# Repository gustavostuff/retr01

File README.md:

Retr01 is an MCU-assisted 8-bit gaming system for arcade and console setups, plus an emulator and a studio for making games and content.

Hardware remains in active development/design. Software, tooling, and documentation track that ongoing specification. The board layout shown above is an early revision and is intended to approximate the planned main PCB.

## Inspirations

1. **NES: readable limits and bold color.** Retr01 uses a 64-color global palette, with up to 25 colors visible on screen at once. Those limits are on purpose. They keep the graphics simple and give every color choice more weight.
2. **SNES: depth without unnecessary complexity.** Two true background planes and pixel-level transparency enable real parallax, layered scenery, and richer scene composition while keeping the graphics pipeline understandable and close to the hardware.
3. **[GameTank](https://gametank.zone/): Open source retro console.** The primary modern inspiration. Retr01 takes the same core ideas of a modest resolution, physical (small) cartridges and a readable multi-chip design that stays explicit instead of hiding behind an FPGA.

## Graphics

The playfield is 128x120 (chunky pixels) scaled to 2x. This means the final render is 256x240, the exact same resolution as the NES, Sega Master System, among others. A whole _game screen_ is 16 tiles wide and 15 tiles tall (a nametable is 240 tile index bytes + 240 _attr_ bytes).

On a higher level, graphics are based on worlds and screens: up to 8 worlds, 64 screens each. That's 512 _TV screens_ of real state + some special/extra screens, PRG, Game music, Game _entities_, etc. All within a 512KB cartridge.

Entities are abstract objects like enemies, players, projectiles, etc. They're made from states, frames, and sprites (a _state_ being something like idle, running, or crouching).

Graphics are tile based, 8x8 pixels, 2bpp.

## Audio

Retr01 uses 8 channels, 5 meant to be used for BGM and the rest for SFX. 

PRG writes notes and a helper chip (an AVR128DB28) mixes them to analog output. The Adventure Kid Waveforms library is used as a built-in sound repository. See [sound.md](docs/sound.md).

## Hardware

The design uses a compact, mostly THT main system board with 19 ICs (CPU + MCUs + SPLDs + some 74xx glue) for both home-console and arcade cabinet builds. That is:

* Home console: TRS ports for the pads. Picture and sound leave on one Kycon KMDGX-9S-AS 9-pin mini-DIN. RGB, CSYNC, composite, mono audio, and +5 V. This is the exact same AV port that the Sega Genesis 2 and Mega Drive 2 made famous.

* Arcade: the same mini-DIN for picture and sound, plus 2x5 headers for sticks and buttons. The JAMMA edge shares those header nets for the controls, and it shares +5 V and GND.

As for the cartridge, it's a small PCB (close to Game Boy size) with an SST39SF040-55-4C-NHE in a PLCC-32 socket, plus a small 8-pin EEPROM for saves. The socket keeps the cart PCB through-hole. 18 gold fingers per side.

Game pads are planned to use a 3-wire connection through any regular male to male audio aux cable (TRS ports on both the main PCB and the pads PCB). A serial protocol + ATtiny chips (on the pads board) will take care of communications.

Retr01 is not a pure TTL/discrete logic design, but it skips the black-box SoC approach entirely. It's a nice middle ground.

Note: the main motherboard is 170 x 120 mm, on a 4-layer stack.

## Software pieces

Retr01 Emu runs .retr01 ROM images.

Retr01 Studio is the authoring tool for worlds, screens, and entities. It includes the emulator for quick playtesting.

BGM tracker:

## Board simulator

A full software simulator of the board already exists. The Sim app uses a C netlist and models the behavior of the ICs, the gamepads, the audio, and the rest of the machine. A finished board has not been tested in real life yet. The design is already clear enough that the whole thing runs there, as a working virtual board.

[Bench tests](docs/irl_bring_up_log/) cover sub-modules of the system, one piece at a time, until the whole system has been tested.

## Doc map

- [hardware.md](docs/hardware.md): Board, BOM, clocks, connectors, cart edge, and JAMMA fingers.
- [pcb.md](docs/pcb.md): Motherboard copper layers, analog keepout, and trace widths.
- [ic-comms-risks.md](docs/ic-comms-risks.md): Shared-bus and multi-clock failure rules.
- [video-graphics.md](docs/video-graphics.md): Resolution, tiles, sprites, the 64-color kit, and the two background layers.
- [world-scrolling.md](docs/world-scrolling.md): World and screen structure, VRAM buffering, sparse map organization, and scrolling over large areas.
- [cartridge.md](docs/cartridge.md): Cartridge hardware, passive memory model, save support, flash workflow, and the basic cart layout.
- [memory.md](docs/memory.md): CPU address map, soft $7Fxx windows, MAP port behavior, .retr01 image format, and flash capacity limits.
- [software-api.md](docs/software-api.md): Runtime model for entities, data structure sizing, C and ASM API, and expected game modes.
- [sound.md](docs/sound.md): Audio architecture, 8-channel software mix, $7F40 register window, 6502 NMI tracker bytecode, and PWM output.
- [irl_bring_up_log/](docs/irl_bring_up_log/): Bench notes. The color PROM check and the Beam X / Beam Y check are the pin netlist and the function of those chips.
- [apps/README.md](apps/README.md): Studio authoring app, Emu runtime, and the discrete-IC board simulation app.

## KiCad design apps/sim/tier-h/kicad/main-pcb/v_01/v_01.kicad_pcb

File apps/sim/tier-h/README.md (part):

# Retr01 Tier H sim (imported)

Imported from the discarded `retr01-bkp-01` board sim. It links this repo's `apps/tools/discrete_ic` and `apps/common`. The UI font is `assets/other` in this tree.

Matches [`docs/hardware.md`](../../../docs/hardware.md) idle-safe rules: soft I/O is `$7Fxx`, and the color PROM is the AT27C256R. Cart `WE#` stays high unless a program cycle drives it, `/SS_S1` and `/SS_S2` idle high, field ALE idles low, and `CPU_RDY` is open-drain with a pull-up. **U2075** is a logic stub for the CXA2075M. **CVOUT** is a video-present flag, not an NTSC waveform. The footprint is the SOP-24. **J2** (KMDGX-9S-AS) carries RGB, CSYNC, COMP, and PWM audio.

# Retr01 Board Simulator

IC-first board simulator for the Retr01 motherboard (arcade + console share one netlist). Separate from Retr01 Studio (authoring). BOM and islands: [`docs/hardware.md`](../../../docs/hardware.md).

**Engine:** discrete IC / island / bus core lives in drop-in [`discrete_ic/`](../../tools/discrete_ic/) (`Ns` / `ns_` API). This tree is the Retr01 board recipe, chips, Host Play, and SDL host. Temporary `R01s*` shims: [`include/retr01_sim/ns_compat.h`](include/retr01_sim/ns_compat.h).

**Goal:** simulate the Retr01 motherboard as discrete ICs (pins, package, datasheet behavior) wired like the real board. End state: boot a cart, accept pad input, show a digital playfield (logical 128x120 inside a 256x240 RGBS field / LCD sink). Accuracy tightens as tests demand it.

## Status (current)

**Netlist / bring-up:** 9 canvas islands (O first) + wired-only E/I/P sprite glue. Soft `$7Fxx` via **MCU-M** on L. Cart image from argv (default `examples/example_01/example_01.retr01`). The console has no USB. Cart programming is the MCU-M bridge.

**UI chrome:** Compact board view. Bottom-right gamepad overlays remain. IC bodies use health-colored 1px outlines from `discrete_ic` (`ns_outline_rgb`).

### Breadboard proto

| Feature | State |
|---------|--------|
| Layout | Nano-style 830-point class, pitch **5** (matches DIP tip lattice). Implementation in `discrete_ic` |
| Interact | Drag, rotate, hole-rail hover highlight |
| IC snap | Tips snap to holes **while dragging** and on rotate / drop |
| Electrical | Soft air wires (LIVE). MANUAL mode UI removed for now |

### LIVE settle

Default path uses soft air-wire settle (LIVE). MANUAL breadboard electrical mode is deferred (HUD control removed).

### Passives tray

Motherboard passives: **64** parts below the ICs, ordered XTAL, CCAP, ECAP, 5V/GND, then R. Cart and pad bypass caps are not in this tray.

| Kind | Role in tray | Notes |
|------|--------------|-------|
| **OSC** | Y1/Y2/Y3 | 3 crystals |
| **CCAP** | 100 nF bypass + crystal loads | 20 + 6 |
| **ECAP** | 220 uF bulk | Polarized flag set (polarity rules later) |
| **5V / GND** | Rail symbols | One of each. IC VCC/GND pins use color instead of air |
| **R** | DAC + 33 ohm series + pull-ups + crystal feedback | 32 total. Only 11 are video DAC |
| **D** | Art present | Not spawned (not on this BOM) |

Sprites: `apps/tools/discrete_ic/assets/passives/` (nano `scaled_down`). Pin pixels and the rotation pivot are in `pin_map.json` (first pin is the pivot). Drag / snap / rotate about that pivot. **Passives are in `R01sBoard.pin_netlist`** (every BOM pin registered; bypass/DAC/series/pull-ups wired in `src/board_schematic.c`). Breadboard strip merge and bus settle through passives are still TODO.

**Preliminary Skidl export (not fab-ready):** [`skidl/export_netlist.sh`](skidl/export_netlist.sh) or `export_tier_h_netlist` + [`scripts/skidl_from_tier_h.py`](../../../scripts/skidl_from_tier_h.py). Outputs under [`skidl/`](skidl/). Illustrative only. The motherboard PCB is not ready for production.

### Canvas islands

| Island | Components (canvas) |
|--------|---------------------|
| O Video | `COMPOSITOR` + `AT27C256R` + `LCD_SINK` |
| A Power+clk | `PWR5V` + `U04`/`U74` (OSC8M ticks PHI2 off-netlist) |
| C CPU + decode | `W65C02S`, `AS6C62256`, decode helper PLD (non-BOM wire entity) |
| G VRAM | 2nd `AS6C62256` + **3x** `SN74HC157` + VRAM glue PLD helper |
| H Beam | Beam X counts dots and drives HSYNC. Beam Y counts lines from that HSYNC and drives VSYNC. The two chips share RES. **`SN74HC574`** holds `$7F02` SX. Pin list matches [irl_bring_up_log/](../../../docs/irl_bring_up_log/). |
| J Cart | Console socket. Flash and save live on **N** |
| K APU + pads | **`AVR128DB28` MCU-S2**: `$7F40`-`$7F5F`, pads `$7F60`/`$7F61`, 8-voice mix + PWM + WAVE monitor |
| L MCU + field | **`AVR128DB28` MCU-M** (soft `$7Fxx` + SPI mailbox master) + **MCU-S1** (OAM apply / field) + field `AS6C62256` + **`SN74HC573`** ALE |
| N Cart module | `SST39SF040` + cart `24C64` (detachable module. Argv `.retr01` is copied into flash). Cart orderable is the PLCC-32 `SST39SF040-55-4C-NHE` |

**Wired on the netlist, not separate canvas frames.** Soft `$7Fxx` settle on board RAM (mirrors MCU-M). OAM/APU CPU/`poke_fe` path flushes via behavioral SPI mailbox to S1/S2. Host Play may still call `r01s_avr128db28_s1_oam_poke` as a preview overlay. **E** pads via MCU-S2, **I** `BG_FETCH`, sprite field fill stats, **P** integration / NMI stats.

Bench-only (wired, not on canvas): `PRG_ROM` fallback when cart does not own `$8000+`.

**Letter note:** Silicon bring-up docs use **N** for the sprite path ([`docs/hardware.md`](../../../docs/hardware.md)). On the sim canvas, **N** is the detachable **cart module** island. Sprite milestones still show as **N** in the health strip detail line.

**BOM:** mounted VIS_IC count includes U2075. Picture and sound leave on J2, the KMDGX-9S-AS mini-DIN. Helper tick domain is 24 MHz.

**Cart load:** argv, or `examples/example_01/example_01.retr01` when omitted, is copied into cart `SST39SF040`. The cart orderable is the PLCC-32 `SST39SF040-55-4C-NHE`. The app then overlays a short boot program that streams the palette and the start screen through `$7Fxx` on the pin netlist. That catchup is the boot wait. Host Play starts after it and drives the wave monitor from `game_logic.c` beside the cart. `board_build` still installs a synthetic image for unit tests that do not call `r01s_board_load_cart`.

**Cart programming:** MCU-M bridge on a seated cart. This tree does not model a USB flasher.

**1_FRAME_DEBUG:** `1_FRAME_DEBUG=true ./sim cart.retr01` logs byte-scale IC traffic (PRG/MAP/VRAM/beam/BG0/sprites/play) into a paginated on-screen panel (`[` `]` or PgUp/PgDn). Logging stops once BG (MAP->VRAM) and the first sprite field fill are done. Full dump: `retr01_sim/debug/frame1_trace.log`.

Why the worker exists: [`CATCHUP_THREADING.md`](CATCHUP_THREADING.md).

### Next (Sim)

- Breadboard strip routing as real MANUAL electrical (beyond soft-gate + overlay)
- Passive polarity (ECAP / diode) and passive netlist
- Optional machine EEPROM (MCU-M 512 B path)
- Retire bring-up Host Play overlay when game PRG owns MAP

## Test layers

```text
  Layer 1: Unit (one IC)
       |
       v
  Layer 2: Island (few ICs + wires). See docs/hardware.md + test_island_abcdeghiojklmnp.c
       |
       v
  Layer 3: System (full board + cart + input + screen)
```

Layer 1: per-chip harness tests in `tests/`. Layer 2: island smoke in `tests/test_island_abcdeghiojklmnp.c`. Layer 3: full netlist + golden cart `output/test.retr01` (`test_host_play_smoke`: catchup + Host Play BG/sprites/APU).

## Cart ROM vs runners (triage)

When something looks wrong on screen, do not assume the `.retr01` is bad and do not assume the emu/sim is bad. Studio authoring, cart image, emu, and sim are different layers.

### Who owns what

| Layer | Artifact | On silicon / runners? | Notes |
|-------|----------|----------------------|--------|
| **Studio editor** | `output/test.r01proj` (+ UI) | **No** | Authoring only. Does not execute PRG |
| **Studio Play** | export then shared emu | **Yes** (via cart) | Same path as **Ctrl+E** + emu render. No Studio-only soft preview |
| **Cart image** | `output/test.retr01` (+ `test_flash.bin`) | **Yes** (flash) | Packed bytes SoT for PRG/CHR/MAP/pals. Layout in [`docs/memory.md`](../../../docs/memory.md) |
| **Color PROM burn** | `test_prom.bin` | **Yes** (motherboard) | Not inside the cart. Kit to R3G3B2. Target part **AT27C256R** |
| **Boot asm listing** | `test_boot.s` | Human-readable only | Binary inside `.retr01` is what runners execute |
| **Emulator** | `retr01_emu` | Software-visible CPU/`$7Fxx` | Loads `.retr01`. Default: PRG catchup streams pals + start MAP. Softboot opt-in (`R01E_SOFTBOOT=1`). Host Play for camera/player. Used by Studio Play and standalone `./emu` |
| **Board sim** | `retr01_sim` | IC / island netlist | Copies argv/default `.retr01` into cart `SST39SF040`. Catchup is pin-level. Softboot opt-in (`R01S_SOFTBOOT=1`). Host Play after catchup |

### What is in `test.retr01` today

| In ROM | Meaning |
|--------|---------|
| Header + pointer table | magic `retr01`, `format_ver` **2** only, world count, **36 B** ptr table (24-bit offs + lens) |
| Other screens + credits | Title + interstitial + credits **pages** in other-screens blob (raw 480 B or RLE). PRG owns presentation |
| Global BG/sprite palettes | 8 BG rows + 8 sprite rows (master indices, not RGB) |
| SPR CHR banks | Real tile bytes from Studio export (4 banks x up to 256 tiles) |
| Entity tables | Per-world type records (origin, hitbox, up to 4 parts) + instance list (type, world x/y) |
| 32 KB PRG | Palette + start-screen MAP stream (`$7F93` -> `$7F08`/`$7F09`/`$7F12`). Scroll/player/warps still **host** Play |
| World table + blobs | CHR banks, screen dir, 480 B present-screen payloads |

| **Not** in ROM | Meaning |
|----------------|---------|
| Host Play motion, camera dead zone, player anim, warps | Emu / sim Host Play + `../common/r01_play_camera.c` (cart-backed). Not a Studio-only preview |
| Host Play BG0 | Emu + sim Host Play: cart BG0 cache, show-through under BG1 color 0, proportional scroll from present extents. Host overlay only (does not drive IC VRAM slots 4-7 or `$7F06`/`$7F07`) |
| Host collision source | Cart flash MAP attrs (`R01_ATTR_SOLID`). PRG collision stub not used by host runners |
| Editor UI state | UI only. Cart boots world **0** |
| Live camera seam streaming (2x2 shift) | Phase 1 PRG loads start screen only |
| Full game loop in 6502 | Still future. Host Play stands in |

### How to tell ROM bug vs runner bug

1. **Hex / dump the cart first.** If the dump is wrong, it is Studio export. If right, blame the runner or soft helpers.
2. **Same `.retr01` on emu and sim.** Both wrong the same way -> ROM/content or shared contract (`02`). Only one fails -> that runner.
3. **Studio Play is cart-backed.** It exports then runs emu. If Studio Play looks wrong, dump the cart. Do not assume a separate Studio compositor.
4. **Call out soft helpers.** `R01E_SOFTBOOT=1` / `R01S_SOFTBOOT=1` are opt-in host poke only.
5. **Color wrong?** Check `*_prom.bin` / board PROM path separately from cart palette indices.

## Architecture (summary)

| Topic | Choice |
|-------|--------|
| Time base | PHI2 half-steps from `OSC8M` (`R01S_PHI2_HALF_NS`). Combinatorial settle. `DELAY=typical|max` prints datasheet path budget (pin netlist stays zero-delay so catchup works) |
| Bus | Settle loop (`R01S_SETTLE_PASSES`). H+L -> hard abort. Undriven -> pull-up HIGH (`$FF`) |
| Wiring | Explicit `wire_*` in `board.c`. Global netlist deferred |
| Boot UX | Worker-thread MAP catchup. See [`CATCHUP_THREADING.md`](CATCHUP_THREADING.md) |
| Perf | [`PERFORMANCE.md`](PERFORMANCE.md) |

**Model:** every IC is an `R01sEntity` (pins + vtable). Islands hold entities. Island groups wire them. `r01s_board_build()` binds the full netlist onto the canvas islands above. Undriven pins pull high. H+L aborts with a bus-fight report.

## Build

From the repo root:

```bash
./scripts/build-all.sh
./scripts/sim-tier.sh
./scripts/unit-tests.sh
```

Developer rebuild of this tree only:

```bash
cmake -S apps/sim/tier-h -B apps/sim/tier-h/build -DCMAKE_BUILD_TYPE=Release
cmake --build apps/sim/tier-h/build -j
ctest --test-dir apps/sim/tier-h/build --output-on-failure
./scripts/sim-tier.sh
```

Needs: CMake, a C compiler, SDL2 (`sdl2` package).

## Run

```bash
./scripts/sim-tier.sh
./scripts/sim-tier.sh examples/example_01/example_01.retr01
./scripts/sim-tier.sh DELAY=typical   # print typ path budget vs PHI2 half
./scripts/sim-tier.sh DELAY=max       # print max (worst-case) path budget
```

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
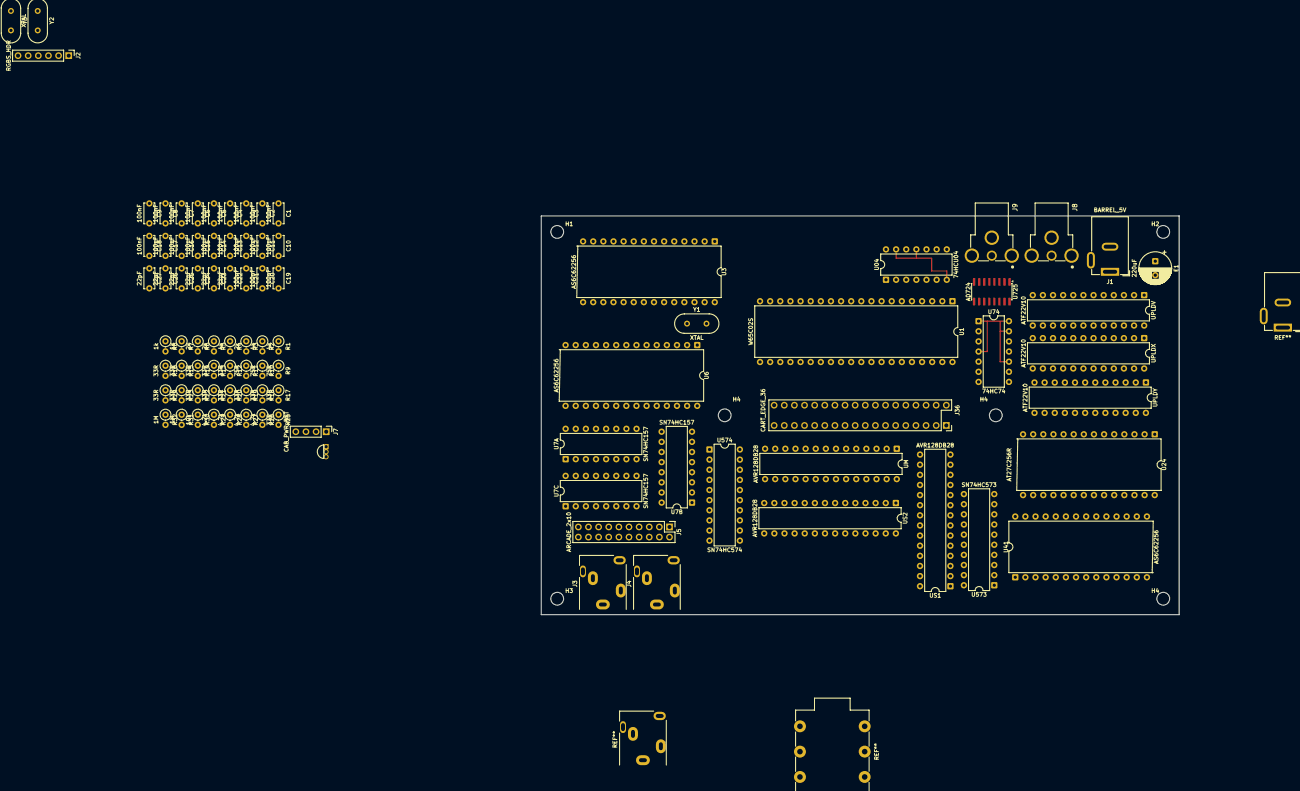
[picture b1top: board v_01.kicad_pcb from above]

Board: 2 copper layers, 160.0 x 100.0 mm, 98 parts (0 on the bottom side), 148 nets, no tracks yet.

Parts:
C1, C2, C3, C4, C5, C6, C7, C8, C9, C10, C11, C12, C13, C14, C15, C16, C17, C18, C19, C20, C21: 100nF; C_Disc_D5.0mm_W2.5mm_P5.00mm
C22, C23, C24, C25, C26, C27: 22pF; C_Disc_D5.0mm_W2.5mm_P5.00mm
E1: 220uF; CP_Radial_D8.0mm_P3.50mm
H1, H2, H3, H4, H4#2, H4#3: MountingHole_3.2mm_M3
J1: BARREL_5V; BarrelJack_GCT_DCJ200-10-A_Horizontal
J2: RGBS_HDR; PinHeader_1x06_P2.54mm_Vertical
J3: TRS_P1; Jack_3.5mm_CUI_SJ1-3515N_Horizontal
J4: TRS_P2; Jack_3.5mm_CUI_SJ1-3515N_Horizontal
J5: ARCADE_2x10; PinHeader_2x10_P2.54mm_Vertical
J7: CAB_PWR_RST; PinHeader_1x04_P2.54mm_Vertical
J8: RCJ-012; CUI_RCJ-014_Audio
J9: RCJ-014; CUI_RCJ-014
J36: CART_EDGE_36; EDAC_395_MoboSocket_2x18_2.54x5.08mm
R1, R2, R4: 4k; R_Axial_DIN0207_L6.3mm_D2.5mm_P2.54mm_Vertical
R3, R5, R6: 2k; R_Axial_DIN0207_L6.3mm_D2.5mm_P2.54mm_Vertical
R7, R8: 1k; R_Axial_DIN0207_L6.3mm_D2.5mm_P2.54mm_Vertical
R9, R10, R11: 75R; R_Axial_DIN0207_L6.3mm_D2.5mm_P2.54mm_Vertical
R12, R13, R14, R15, R16, R17, R18, R19, R20, R21, R22, R23, R24, R25: 33R; R_Axial_DIN0207_L6.3mm_D2.5mm_P2.54mm_Vertical
R26, R27, R28, R29: 4.7k; R_Axial_DIN0207_L6.3mm_D2.5mm_P2.54mm_Vertical
R30: 10k; R_Axial_DIN0207_L6.3mm_D2.5mm_P2.54mm_Vertical
R31, R32: 1M; R_Axial_DIN0207_L6.3mm_D2.5mm_P2.54mm_Vertical
U1: W65C02S; DIP-40_W15.24mm
U3, U6, U41: AS6C62256; DIP-28_W15.24mm
U04: 74HCU04; DIP-14_W7.62mm_74HCU04
U7A, U7B, U7C: SN74HC157; DIP-16_W7.62mm
U24: AT27C256R; DIP-28_W15.24mm
U74: 74HC74; DIP-14_W7.62mm_74HC74
U130: MCP130; TO-92_Inline
U573: SN74HC573; DIP-20_W7.62mm
U574: SN74HC574; DIP-20_W7.62mm
U725: AD724; SOIC-16_3.9x9.9mm_P1.27mm
UM: AVR128DB28; DIP-28_W7.62mm
UPLDV: ATF22V10; DIP-24_W7.62mm
UPLDX: ATF22V10; DIP-24_W7.62mm
UPLDY: ATF22V10; DIP-24_W7.62mm
US1, US2: AVR128DB28; DIP-28_W7.62mm
Y1, Y2, Y3: XTAL; Crystal_HC49-U_Vertical

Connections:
+5V: C1.1, C2.1, C3.1, C4.1, C5.1, C6.1, C7.1, C8.1, C9.1, C10.1, C11.1, C12.1, C13.1, C14.1, C15.1, C16.1, C17.1, C18.1, C19.1, C20.1, E1.1, J1.1 (+5V), J3.T (+5V), J4.T (+5V), J7.1, J36.3, J36.4, R26.1, R27.1, R28.1, R29.1, R30.1, U1.8 (VDD), U3.28 (VCC), U04.14 (VCC), U6.28 (VCC), U7A.16 (VCC), U7B.16 (VCC), U7C.16 (VCC), U24.28 (VCC), U41.28 (VCC), U74.14 (VCC), U130.2 (VDD), U573.20 (VCC), U574.20 (VCC), U725.1 (STND), U725.4 (APOS), U725.5 (ENCD), U725.14 (DPOS), U725.15 (VSYNC), UM.6, UM.14, UM.20, UPLDV.24, UPLDX.24, UPLDY.24, US1.6, US1.14, US1.20, US2.6, US2.14, US2.20
ALE_LE: U573.11 (LE), US1.16
AUDIO_OUT: J8.2 (SIGNAL), US2.17
CART_D0: J36.8, R14.2
CART_D1: J36.10, R15.2
CART_D2: J36.12, R16.2
CART_D3: J36.14, R17.2
CART_D4: J36.16, R18.2
CART_D5: J36.18, R19.2
CART_D6: J36.20, R20.2
CART_D7: J36.22, R21.2
CART_OE#_1: J36.24, R22.2
CART_SCL: J36.6, R25.2
CART_SDA: J36.5, R24.2
CART_WE#_1: J36.36, R23.2
CLK_10M: U74.5 (1Q), U74.11 (2CLK)
CLK_10M_INV: U74.2 (1D), U74.6 (1/Q)
CLK_21M: U04.4 (2Y), U74.3 (1CLK)
COMPOSITE_OUT: J9.2 (SIGNAL), U725.10 (COMP)
CPU_A0: J36.7, U1.9 (A0), U3.10 (A0), U7A.2 (I0a)
CPU_A1: J36.9, U1.10 (A1), U3.9 (A1), U7A.5 (I0b)
CPU_A2: J36.11, U1.11 (A2), U3.8 (A2), U7A.11 (I0c)
CPU_A3: J36.13, U1.12 (A3), U3.7 (A3), U7A.14 (I0d)
CPU_A4: J36.15, U1.13 (A4), U3.6 (A4), U7B.2 (I0a)
CPU_A5: J36.17, U1.14 (A5), U3.5 (A5), U7B.5 (I0b)
CPU_A6: J36.19, U1.15 (A6), U3.4 (A6), U7B.11 (I0c)
CPU_A7: J36.21, U1.16 (A7), U3.3 (A7), U7B.14 (I0d)
CPU_A8: J36.23, U1.17 (A8), U3.25 (A8), U7C.2 (I0a)
CPU_A9: J36.25, U1.18 (A9), U3.24 (A9), U7C.5 (I0b)
CPU_A10: J36.27, U1.19 (A10), U3.21 (A10), U7C.11 (I0c)
CPU_A11: J36.29, U1.20 (A11), U3.23 (A11), U7C.14 (I0d)
CPU_A12: J36.31, U1.22 (A12), U3.2 (A12)
CPU_A13: J36.33, U1.23 (A13), U3.26 (A13)
CPU_A14: U1.24 (A14), U3.1 (A14)
CPU_D0: R14.1, U1.33 (D0), U3.11 (Q0), U6.11 (Q0), U574.2 (D0), UM.22
CPU_D1: R15.1, U1.32 (D1), U3.12 (Q1), U6.12 (Q1), U574.3 (D1), UM.23
CPU_D2: R16.1, U1.31 (D2), U3.13 (Q2), U6.13 (Q2), U574.4 (D2), UM.26
CPU_D3: R17.1, U1.30 (D3), U3.15 (Q3), U6.15 (Q3), U574.5 (D3), UM.27
CPU_D4: R18.1, U1.29 (D4), U3.16 (Q4), U6.16 (Q4), U574.6 (D4), UM.28
CPU_D5: R19.1, U1.28 (D5), U3.17 (Q5), U6.17 (Q5), U574.7 (D5), UM.1
CPU_D6: R20.1, U1.27 (D6), U3.18 (Q6), U6.18 (Q6), U574.8 (D6), UM.12
CPU_D7: R21.1, U1.26 (D7), U3.19 (Q7), U6.19 (Q7), U574.9 (D7), UM.13
CPU_IRQ#: U1.4 (IRQB), UPLDY.1
CPU_PHI2: R12.2, U1.37 (PHI2)
CPU_RDY: R29.2, U1.2 (RDY), UM.8
CPU_RES#: J7.3, R30.2, U1.40 (RESB), U130.1 (RESET#)
CSYNC: J2.4 (CSYNC), U725.16 (HSYNC), UPLDV.14
DOT: R13.1, U74.9 (2Q)
DOT_INV: U74.8 (2/Q), U74.12 (2D)
FSC_FIN: C23.1, U725.3 (FIN), Y3.1
FSC_XTAL: C24.1, Y3.2
GND: C1.2, C2.2, C3.2, C4.2, C5.2, C6.2, C7.2, C8.2, C9.2, C10.2, C11.2, C12.2, C13.2, C14.2, C15.2, C16.2, C17.2, C18.2, C19.2, C20.2, C21.2, C22.2, C23.2, C24.2, C25.2, C26.2, C27.2, E1.2, J1.2 (GND), J1.3 (GND), J3.S (GND), J4.S (GND), J5.17, J5.18, J5.19, J5.20, J7.2, J7.4, J8.1A (GND), J8.1B (GND), J8.1C (GND), J9.1A (GND), J9.1B (GND), J9.1C (GND), J36.1, J36.2, J36.35, R9.2, R10.2, R11.2, U1.21 (VSS), U3.14 (GND), U04.7 (GND), U6.14 (GND), U7A.8 (GND), U7B.8 (GND), U7C.8 (GND), U24.2 (A12), U24.3 (A7), U24.4 (A6), U24.14 (GND), U24.20 (~CE), U24.21 (A10), U24.22 (~OE), U24.23 (A11), U24.24 (A9), U24.25 (A8), U24.26 (A13), U41.14 (GND), U74.7 (GND), U130.3 (VSS), U573.1 (OE#), U573.10 (GND), U574.1 (OE#), U574.10 (GND), U725.2 (AGND), U725.12 (SELECT), U725.13 (DGND), UM.15, UM.21, UPLDV.12, UPLDX.12, UPLDY.12, US1.15, US1.21, US2.15, US2.21
LB_A0: U41.10 (A0), U573.19 (Q7)
LB_A1: U41.9 (A1), U573.18 (Q6)
LB_A2: U41.8 (A2), U573.17 (Q5)
LB_A3: U41.7 (A3), U573.16 (Q4)
LB_A4: U41.6 (A4), U573.15 (Q3)
LB_A5: U41.5 (A5), U573.14 (Q2)
LB_A6: U41.4 (A6), U573.13 (Q1)
LB_A7: U41.3 (A7), U573.12 (Q0)
LINEBUF_WE#: U41.27 (~WE), US1.17
MCU_SCL: R25.1, R28.2, UM.25
MCU_SDA: R24.1, R27.2, UM.24
PAD1_DATA: J3.R (DATA), J4.R (DATA), U7B.10 (I1c)
PAD_DATA_BUS: R26.2, US2.16
PHI2: R12.1, U04.8 (4Y)
PROM_O0: R8.1, U24.11 (D0)
PROM_O1: R7.1, U24.12 (D1)
PROM_O2: R6.1, U24.13 (D2)
PROM_O3: R5.1, U24.15 (D3)
PROM_O4: R4.1, U24.16 (D4)
PROM_O5: R3.1, U24.17 (D5)
PROM_O6: R2.1, U24.18 (D6)
PROM_O7: R1.1, U24.19 (D7)
SCROLL_CLK_1: J3.RN (NC), J3.TN (NC), J4.RN (NC), J4.TN (NC), U04.10 (5Y), U04.12 (6Y), U574.11 (CLK)
SIG_J5_P1_TO_US2_P22: J5.1, US2.22
SIG_J5_P3_TO_US2_P23: J5.3, US2.23
SIG_J5_P4_TO_US2_P3: J5.4, US2.3
SIG_J5_P5_TO_US2_P24: J5.5, US2.24
SIG_J5_P7_TO_US2_P25: J5.7, US2.25
SIG_J5_P8_TO_US2_P5: J5.8, US2.5
SIG_J5_P9_TO_US2_P26: J5.9, US2.26
SIG_J5_P11_TO_US2_P27: J5.11, US2.27
SIG_J5_P13_TO_US2_P28: J5.13, US2.28
SIG_J5_P15_TO_US2_P1: J5.15, US2.1
SIG_U6_P3_TO_U7B_P12: U6.3 (A7), U7B.12 (Zd)
SIG_U6_P4_TO_U7B_P9: U6.4 (A6), U7B.9 (Zc)
SIG_U6_P5_TO_U7B_P7: U6.5 (A5), U7B.7 (Zb)
SIG_U6_P6_TO_U7B_P4: U6.6 (A4), U7B.4 (Za)
SIG_U6_P8_TO_U7A_P9: U6.8 (A2), U7A.9 (Zc)
SIG_U6_P9_TO_U7A_P7: U6.9 (A1), U7A.7 (Zb)
SIG_U6_P10_TO_U7A_P4: U6.10 (A0), U7A.4 (Za)
SIG_U6_P21_TO_U7C_P9: U6.21 (A10), U7C.9 (Zc)
SIG_U6_P23_TO_U7C_P12: U6.23 (A11), U7C.12 (Zd)
SIG_U6_P25_TO_U7C_P4: U6.25 (A8), U7C.4 (Za)
SIG_U7A_P12_TO_U6_P7: U6.7 (A3), U7A.12 (Zd)
SIG_U7C_P7_TO_U6_P24: U6.24 (A9), U7C.7 (Zb)
SIG_U24_P5_TO_UPLDV_P20: U24.5 (A5), UPLDV.20
SIG_U24_P7_TO_UPLDV_P18: U24.7 (A3), UPLDV.18
SIG_U41_P1_TO_US1_P9: U41.1 (A14), US1.9
SIG_U41_P2_TO_US1_P7: U41.2 (A12), US1.7
SIG_U41_P11_BUS: U41.11 (Q0), U573.2 (D0), US1.22
SIG_U41_P12_BUS: U41.12 (Q1), U573.3 (D1), US1.23
SIG_U41_P13_BUS: U41.13 (Q2), U573.4 (D2), US1.24
SIG_U41_P15_BUS: U41.15 (Q3), U573.5 (D3), US1.25
SIG_U41_P17_BUS: U41.17 (Q5), U573.7 (D5), US1.27
SIG_U41_P18_BUS: U41.18 (Q6), U573.8 (D6), US1.28
SIG_U41_P19_BUS: U41.19 (Q7), U573.9 (D7), US1.1
SIG_U41_P21_TO_US1_P4: U41.21 (A10), US1.4
SIG_U41_P24_TO_US1_P3: U41.24 (A9), US1.3
SIG_U41_P25_TO_US1_P2: U41.25 (A8), US1.2
SIG_U41_P26_TO_US1_P8: U41.26 (A13), US1.8
SIG_U573_P6_BUS: U41.16 (Q4), U573.6 (D4), US1.26
SIG_UM_P18_TO_US1_P18: UM.18, US1.18
SIG_UPLDV_P15_TO_U24_P10: U24.10 (A0), UPLDV.15
SIG_UPLDV_P16_TO_U24_P9: U24.9 (A1), UPLDV.16
SIG_UPLDV_P17_TO_U24_P8: U24.8 (A2), UPLDV.17
SIG_UPLDV_P19_TO_U24_P6: U24.6 (A4), UPLDV.19
SIG_UPLDX_P1_TO_R13_P2: R13.2, UPLDX.1
SIG_UPLDX_P13_TO_UPLDY_P2: UPLDX.13, UPLDY.2
SIG_UPLDX_P14_TO_UPLDY_P3: UPLDX.14, UPLDY.3
SIG_UPLDX_P19_TO_UPLDY_P8: UPLDX.19, UPLDY.8
SIG_UPLDY_P4_TO_UPLDX_P15: UPLDX.15, UPLDY.4
SIG_UPLDY_P5_TO_UPLDX_P16: UPLDX.16, UPLDY.5
SIG_UPLDY_P6_TO_UPLDX_P17: UPLDX.17, UPLDY.6
SIG_UPLDY_P7_TO_UPLDX_P18: UPLDX.18, UPLDY.7
SIG_UPLDY_P9_TO_UPLDX_P20: UPLDX.20, UPLDY.9
SIG_US1_P5_TO_U41_P23: U41.23 (A11), US1.5
SIG_US2_P2_TO_J5_P2: J5.2, US2.2
SIG_US2_P4_TO_J5_P6: J5.6, US2.4
SIG_US2_P7_TO_J5_P10: J5.10, US2.7
SIG_US2_P8_TO_J5_P12: J5.12, US2.8
SIG_US2_P9_TO_J5_P14: J5.14, US2.9
SIG_US2_P18_TO_J5_P16: J5.16, US2.18
SPI_MISO: UM.3, US1.11, US2.11
SPI_MOSI: UM.2, US1.10, US2.10
SPI_SCK: UM.4, US1.12, US2.12
SS_S1#: UM.5, US1.13
SS_S2#: UM.11, US2.13
U04_SPARE_IN: U04.11 (5A), U04.13 (6A)
U74_PRE_CLR#: U74.1 (1CLR#), U74.4 (1PRE#), U74.10 (2PRE#), U74.13 (2CLR#)
VIDEO_BLUE: J2.3 (B), R7.2, R8.2, R11.1, U725.8 (BIN)
VIDEO_GREEN: J2.2 (G), R4.2, R5.2, R6.2, R10.1, U725.7 (GIN)
VIDEO_RED: J2.1 (R), R1.2, R2.2, R3.2, R9.1, U725.6 (RIN)
XTAL_10M_IN: C25.1, R31.1, U04.5 (3A), Y1.1
XTAL_10M_OUT: C26.1, R31.2, U04.6 (3Y), U04.9 (4A), Y1.2
XTAL_DOT_IN: C21.1, R32.1, U04.1 (1A), Y2.1
XTAL_DOT_OUT: C22.1, R32.2, U04.2 (1Y), U04.3 (2A), Y2.2

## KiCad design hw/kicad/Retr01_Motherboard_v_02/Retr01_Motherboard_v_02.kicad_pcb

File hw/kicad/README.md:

# Retr01 KiCad projects

Single home for PCB / project files and the custom footprint library.

**Netlists** still come from [`app/schematic_generator/`](../../app/schematic_generator/) (`python generate.py`). Import into the live projects below. Quilter Circuit Comprehension notes: [`docs/passive_rf_etc.md`](../../docs/passive_rf_etc.md) (power nets + bypass caps).

## Layout

| Path | Role |
|------|------|
| **[`motherboard/`](motherboard/)** | **Live** motherboard project. Open `Retr01_Motherboard.kicad_pro` |
| **[`cartridge/`](cartridge/)** | **Live** cartridge project. Open `Retr01_Cartridge.kicad_pro` |
| **[`Retr01_Lib.pretty/`](Retr01_Lib.pretty/)** | Custom footprints (TRS, RCA, cart gold fingers). Both projects point here via `fp-lib-table` |
| **[`archive/`](archive/)** | Old boards and Quilter downloads (not the working copy) |

```text
hw/kicad/
+-- Retr01_Lib.pretty/     # authority footprint lib
+-- motherboard/           # live mobo (from former v07)
+-- cartridge/             # live cart
+-- archive/
    +-- motherboard_v01/   # first KiCad project
    +-- snapshots_v02/     # intermediate v02-v07 saves
    +-- quilter/           # Quilter candidate exports
```

## Cartridge gold fingers

Cart netlist `J36` uses `Retr01_Lib:Cart_Edge_2x18_P2.54mm` (pads **1-18** = A / F.Cu, **19-36** = B / B.Cu). Motherboard `J36` stays on the PinSocket stand-in.

**Import / swap in Pcbnew:**

1. Draw `Edge.Cuts` (~**55 x 55 mm**, thickness **1.6 mm**, **4-layer** F/GND/GND/B).
2. `File` -> `Import` -> `Netlist` -> `app/schematic_generator/output/retr01_cart.net` (or Update PCB from schematic if you keep a sch).
3. If an old PinSocket `J36` is still on the board: delete it, then Update PCB so the gold-finger footprint appears.
4. Place `J36` with origin on the insert edge. Pads point into the board (+X in the footprint). Silk **A1** marks side A pin 1.
5. Place U40 / U50 / caps and route.

**Quilter (cart):** Circuit Comprehension checklist is in [`docs/passive_rf_etc.md`](../../docs/passive_rf_etc.md#quilter-circuit-comprehension---cartridge-pcb) (4-layer SIG/GND/GND/SIG, full-board `+5V` on outers, `GND` on inners, stubs pour off, `CD1`/`CD2` only). KiCad: `J36` and `Edge.Cuts` locked; copper zones cover the full outline. After reopen, **Edit -> Fill All Zones**.

Confirm `fp-lib-table` resolves `Retr01_Lib` (already set for `cartridge/`).

SKiDL / schem generator uses the same footprints via a symlink: `app/schematic_generator/library/Retr01_Lib.pretty` -> this folder.

## Archive policy

Do not edit under `archive/` for new layout work. Copy a snapshot into `motherboard/` only if you intentionally revive an old spin. Quilter zips and candidate PCBs stay in `archive/quilter/`.

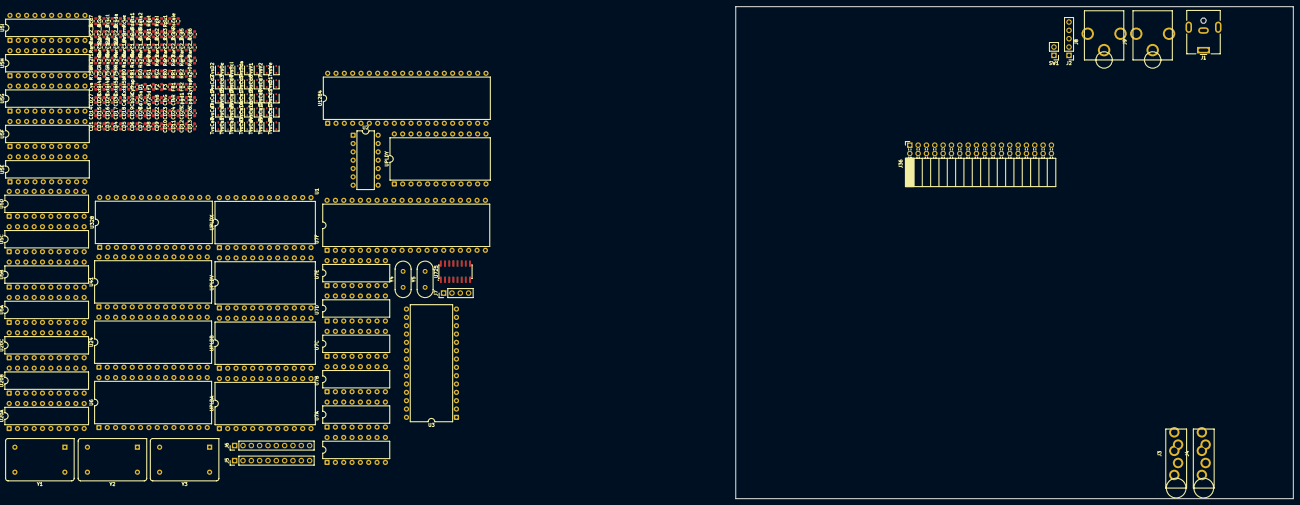
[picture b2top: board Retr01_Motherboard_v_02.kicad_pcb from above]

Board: 4 copper layers, 170.0 x 150.0 mm, 198 parts (0 on the bottom side), 212 nets, no tracks yet.

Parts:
CD1, CD2, CD3, CD4, CD5, CD6, CD7, CD8, CD9, CD10, CD11, CD12, CD13, CD14, CD15, CD16, CD17, CD18, CD19, CD20, CD21, CD22, CD23, CD24, CD25, CD26, CD27, CD28, CD29, CD30: C_100N; C_0603_1608Metric
Caud: C_10U_AUD; C_0603_1608Metric
Cbulk: C_BULK; C_0603_1608Metric
Cd725a, Cd725d: C_100N; C_0603_1608Metric
CinB: C_100N; C_0603_1608Metric
CinG: C_100N; C_0603_1608Metric
CinR: C_100N; C_0603_1608Metric
Cpad1, Cpad2: C_100N; C_0603_1608Metric
Cva: C_10U; C_0603_1608Metric
Cxtal4a, Cxtal4b, Cxtal5a, Cxtal5b: C_22P; C_0603_1608Metric
Cytrap: C_100N; C_0603_1608Metric
D1: SCHOTTKY; R_0603_1608Metric
F1, F2, F3: PPTC; R_0603_1608Metric
FB1, FB2: FERRITE; R_0603_1608Metric
J1: BARREL_5V; BarrelJack_CUI_PJ-063AH_Horizontal
J2: RGBS_HDR; PinHeader_1x05_P2.54mm_Vertical
J3: TRS_P1; Jack_3.5mm_Switchcraft_35RAPC2BVN4_Vertical
J4: TRS_P2; Jack_3.5mm_Switchcraft_35RAPC2BVN4_Vertical
J5: ARCADE_P1; PinHeader_1x10_P2.54mm_Vertical
J6: ARCADE_P2; PinHeader_1x10_P2.54mm_Vertical
J7: CAB_PWR_RST; PinHeader_1x04_P2.54mm_Vertical
J8: AUDIO_OUT; CUI_RCJ-01x_Vertical
J9: COMPOSITE_OUT; CUI_RCJ-01x_Vertical
J36: CART_EDGE_36; PinSocket_2x18_P2.54mm_Horizontal
Lytrap: L_YTRAP; L_0603_1608Metric
R75B, R75C, R75G, R75R: R_75; R_0603_1608Metric
RB0: R_2K; R_0603_1608Metric
RB1: R_1K; R_0603_1608Metric
RG0: R_4K; R_0603_1608Metric
RG1: R_2K; R_0603_1608Metric
RG2: R_1K; R_0603_1608Metric
RR0: R_4K; R_0603_1608Metric
RR1: R_2K; R_0603_1608Metric
RR2: R_1K; R_0603_1608Metric
Ra2r0, Ra2r1, Ra2r2, Ra2r3, Ra2r4, Ra2r5, Ra2r6, Ra2r7: R_20K; R_0603_1608Metric
Rar0, Rar1, Rar2, Rar3, Rar4, Rar5, Rar6: R_10K; R_0603_1608Metric
Rarc1_1, Rarc1_2, Rarc1_3, Rarc1_4, Rarc1_5, Rarc1_6, Rarc1_7, Rarc1_8, Rarc2_1, Rarc2_2, Rarc2_3, Rarc2_4, Rarc2_5, Rarc2_6, Rarc2_7, Rarc2_8: R_47; R_0603_1608Metric
Raterm: R_20K; R_0603_1608Metric
Raud: R_1K; R_0603_1608Metric
Rcd0, Rcd1, Rcd2, Rcd3, Rcd4, Rcd5, Rcd6, Rcd7: R_33; R_0603_1608Metric
Rcoe: R_33; R_0603_1608Metric
Rcscl: R_33; R_0603_1608Metric
Rcsda: R_33; R_0603_1608Metric
Rcwe: R_33; R_0603_1608Metric
Rdata1, Rdata2: R_47; R_0603_1608Metric
Rdot: R_33; R_0603_1608Metric
Rphi: R_33; R_0603_1608Metric
Rpu1: R_4K7; R_0603_1608Metric
Rscale: R_10K; R_0603_1608Metric
SW1: SCALE_SW; PinHeader_1x02_P2.54mm_Vertical
TvsCa0, TvsCa1, TvsCa2, TvsCa3, TvsCa4, TvsCa5, TvsCa6, TvsCa7, TvsCa8, TvsCa9, TvsCa10, TvsCa11, TvsCa12, TvsCa13, TvsCa14, TvsCa15, TvsCa16, TvsCa17, TvsCa18: TVS_5V; D_SOD-323
TvsCd0, TvsCd1, TvsCd2, TvsCd3, TvsCd4, TvsCd5, TvsCd6, TvsCd7: TVS_5V; D_SOD-323
TvsD1, TvsD2: TVS_5V; D_SOD-323
TvsOe: TVS_5V; D_SOD-323
TvsScl: TVS_5V; D_SOD-323
TvsSda: TVS_5V; D_SOD-323
TvsV1, TvsV2: TVS_5V; D_SOD-323
TvsWe: TVS_5V; D_SOD-323
U1: W65C02S; DIP-40_W15.24mm
U2: SN74HC14; DIP-14_W7.62mm
U3, U6, U41: AS6C62256; DIP-28_W15.24mm
U5A, U5B, U5C, U5D, U5E, U5F, U5G, U5H, U5I: SN74HC573; DIP-20_W7.62mm
U7A, U7B, U7C, U7D, U7E, U7F: SN74HC157; DIP-16_W7.62mm
U20A, U20B, U20C: SN74HC245; DIP-20_W7.62mm
U24: AT27C256R; DIP-28_W15.24mm
U328: ATmega328P; DIP-28_W15.24mm
U725: AD725; SOIC-16_3.9x9.9mm_P1.27mm
U1284: ATmega1284P; DIP-40_W15.24mm
UPLDA: ATF22V10; DIP-24_W15.24mm
UPLDB: ATF22V10; DIP-24_W15.24mm
UPLDV: ATF22V10; DIP-24_W15.24mm
UPLDX: ATF22V10; DIP-24_W15.24mm
UPLDY: ATF22V10; DIP-24_W15.24mm
Y1: OSC8M; Oscillator_DIP-14
Y2: OSC_DOT; Oscillator_DIP-14
Y3: OSC_4FSC; Oscillator_DIP-14
Y4: XTAL_20M; Crystal_HC49-U_Vertical
Y5: XTAL_16M; Crystal_HC49-U_Vertical

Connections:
+5V: CD1.1, CD2.1, CD3.1, CD4.1, CD5.1, CD6.1, CD7.1, CD8.1, CD9.1, CD10.1, CD11.1, CD12.1, CD13.1, CD14.1, CD15.1, CD16.1, CD17.1, CD18.1, CD19.1, CD20.1, CD21.1, CD22.1, CD23.1, CD24.1, CD25.1, CD26.1, CD27.1, CD28.1, CD29.1, CD30.1, Cbulk.1, Cd725a.1, Cd725d.1, Cva.1, F2.1, F3.1, FB1.2, FB2.1, FB2.2, J7.1, J36.2, J36.20, Rpu1.1, SW1.2, U1.8, U2.14, U3.28, U5A.20, U5B.20, U5C.20, U5D.20, U5E.20, U5F.20, U5G.20, U5H.20, U5I.20, U6.28, U7A.16, U7B.16, U7C.16, U7D.16, U7E.16, U7F.16, U20A.20, U20B.20, U20C.20, U24.28, U41.28, U328.7, U725.1, U725.4, U725.5, U725.14, U725.15, U1284.10, UPLDA.24, UPLDB.24, UPLDV.24, UPLDX.24, UPLDY.24, Y1.1, Y1.14, Y2.1, Y2.14, Y3.1, Y3.14
AD725_BIN: CinB.2, U725.8
AD725_GIN: CinG.2, U725.7
AD725_RIN: CinR.2, U725.6
ASUM0: Ra2r0.2, Rar0.1, Raterm.1
ASUM1: Ra2r1.2, Rar0.2, Rar1.1
ASUM2: Ra2r2.2, Rar1.2, Rar2.1
ASUM3: Ra2r3.2, Rar2.2, Rar3.1
ASUM4: Ra2r4.2, Rar3.2, Rar4.1
ASUM5: Ra2r5.2, Rar4.2, Rar5.1
ASUM6: Ra2r6.2, Rar5.2, Rar6.1
AUD0: Ra2r0.1, U328.14
AUD1: Ra2r1.1, U328.15
AUD2: Ra2r2.1, U328.16
AUD3: Ra2r3.1, U328.17
AUD4: Ra2r4.1, U328.18
AUD5: Ra2r5.1, U328.19
AUD6: Ra2r6.1, U328.23
AUD7: Ra2r7.1, U328.24
AUDIO_OUT: Caud.2, J8.1
AUDIO_SUM: Caud.1, Ra2r7.2, Rar6.2, Raud.1
BEAM_LB_A9: U7D.6, U7E.6, U7F.6, UPLDX.16, UPLDY.3
BEAM_LB_A10: U7D.10, U7E.10, U7F.10, UPLDX.17, UPLDY.4
BEAM_LB_A11: U7D.13, U7E.13, U7F.13, UPLDX.18, UPLDY.5
BEAM_Y0: U7D.3, U7E.3, U7F.3, UPLDX.15, UPLDY.2
BEAM_Y4: UPLDX.19, UPLDY.6
BEAM_Y5: UPLDX.20, UPLDY.7
BEAM_Y6: UPLDX.21, UPLDY.8
BEAM_Y7: UPLDX.22, UPLDY.9
CART_A0: J36.4, TvsCa0.1, U1.9, U3.10, UPLDA.2
CART_A5: J36.9, TvsCa5.1, U1.14, U3.5, UPLDA.7
CART_A6: J36.10, TvsCa6.1, U1.15, U3.4, UPLDA.8
CART_A7: J36.11, TvsCa7.1, U1.16, U3.3, UPLDA.9
CART_A8: J36.12, TvsCa8.1, U1.17, U3.25
CART_A11: J36.15, TvsCa11.1, U1.20, U3.23
CART_A13: J36.17, TvsCa13.1, U1.23, U3.26
CART_A14: J36.31, TvsCa14.1, U5G.19
CART_A15: J36.32, TvsCa15.1, U5H.18
CART_A16: J36.33, TvsCa16.1, U5I.17
CART_A17: J36.34, TvsCa17.1, U5I.16
CART_A18: J36.35, TvsCa18.1, U5I.15
CART_D0: J36.22, Rcd0.2, TvsCd0.1
CART_D0_MCU: Rcd0.1, U20C.18
CART_D1: J36.23, Rcd1.2, TvsCd1.1
CART_D1_MCU: Rcd1.1, U20C.17
CART_D2: J36.24, Rcd2.2, TvsCd2.1
CART_D2_MCU: Rcd2.1, U20C.16
CART_D3: J36.25, Rcd3.2, TvsCd3.1
CART_D3_MCU: Rcd3.1, U20C.15
CART_D4: J36.26, Rcd4.2, TvsCd4.1
CART_D4_MCU: Rcd4.1, U20C.14
CART_D5: J36.27, Rcd5.2, TvsCd5.1
CART_D5_MCU: Rcd5.1, U20C.13
CART_D6: J36.28, Rcd6.2, TvsCd6.1
CART_D6_MCU: Rcd6.1, U20C.12
CART_D7: J36.29, Rcd7.2, TvsCd7.1
CART_D7_MCU: Rcd7.1, U20C.11
CART_OE_MCU: Rcoe.1, UPLDB.20
CART_OE_N: J36.30, Rcoe.2, TvsOe.1
CART_WE_MCU: Rcwe.1, UPLDB.21
CART_WE_N: J36.36, Rcwe.2, TvsWe.1
COMPOSITE_OUT: J9.1, R75C.2
COMP_RAW: R75C.1, U725.10
CPU_A9: J36.13, TvsCa9.1, U1.18, U3.24
CPU_A10: J36.14, TvsCa10.1, U1.19, U3.21
CPU_A12: J36.16, TvsCa12.1, U1.22, U3.2
CPU_A14: U1.24, U3.1
CPU_A_LO1: J36.5, TvsCa1.1, U1.10, U3.9, UPLDA.3
CPU_A_LO2: J36.6, TvsCa2.1, U1.11, U3.8, UPLDA.4
CPU_A_LO3: J36.7, TvsCa3.1, U1.12, U3.7, UPLDA.5
CPU_A_LO4: J36.8, TvsCa4.1, U1.13, U3.6, UPLDA.6
CPU_BE: U1.36, UPLDA.10
CPU_D0: U1.33, U3.11, U5A.2, U5B.2, U5C.2, U5D.2, U5E.2, U5F.2, U5G.2, U5H.2, U5I.2, U6.11, U7A.2, U7A.3, U20A.2, U20A.18, U20C.2, U328.2, U1284.24, UPLDB.2
CPU_D3: U1.30, U3.15, U5A.5, U5B.5, U5C.5, U5D.5, U5E.5, U5F.5, U5G.5, U5H.5, U5I.5, U6.15, U7A.13, U7A.14, U20A.5, U20A.15, U20C.5, U328.5, U1284.27, UPLDB.5
CPU_D4: U1.29, U3.16, U5A.6, U5B.6, U5C.6, U5D.6, U5E.6, U5F.6, U5G.6, U5H.6, U5I.6, U6.16, U7B.2, U7B.3, U20A.6, U20A.14, U20C.6, U328.6, U1284.28, UPLDB.6
CPU_RWB: U1.34, UPLDA.11
CPU_VA2: U1.31, U3.13, U5A.4, U5B.4, U5C.4, U5D.4, U5E.4, U5F.4, U5G.4, U5H.4, U5I.4, U6.13, U7A.10, U7A.11, U20A.4, U20A.16, U20C.4, U328.4, U1284.26, UPLDB.4
CPU_VA6: U1.27, U3.18, U5A.8, U5B.8, U5C.8, U5D.8, U5E.8, U5F.8, U5G.8, U5H.8, U5I.8, U6.18, U7B.10, U7B.11, U20A.8, U20A.12, U20C.8, U328.12, U1284.20, UPLDB.8
CPU_VA8: U7C.2, U7C.3, UPLDB.10
CSYNC: J2.4, U725.16, UPLDV.14
DIR_CART245: U20C.1, UPLDB.18
DIR_CPU245: U7C.13, U7C.14, U20A.1, UPLDB.14
DIR_VID245: U6.26, U20B.1, UPLDB.16
DOT_CLK: Rdot.2, UPLDX.1
DOT_SRC: Rdot.1, Y2.8
FSC4: U725.3, Y3.8
GND: CD1.2, CD2.2, CD3.2, CD4.2, CD5.2, CD6.2, CD7.2, CD8.2, CD9.2, CD10.2, CD11.2, CD12.2, CD13.2, CD14.2, CD15.2, CD16.2, CD17.2, CD18.2, CD19.2, CD20.2, CD21.2, CD22.2, CD23.2, CD24.2, CD25.2, CD26.2, CD27.2, CD28.2, CD29.2, CD30.2, Cbulk.2, Cd725a.2, Cd725d.2, Cpad1.2, Cpad2.2, Cva.2, Cxtal4a.2, Cxtal4b.2, Cxtal5a.2, Cxtal5b.2, Cytrap.2, J1.2, J1.MP, J2.5, J3.1, J4.1, J5.9, J5.10, J6.9, J6.10, J7.2, J7.4, J8.2, J9.2, J36.1, J36.18, J36.19, R75B.2, R75G.2, R75R.2, Raterm.2, Rscale.2, TvsCa0.2, TvsCa1.2, TvsCa2.2, TvsCa3.2, TvsCa4.2, TvsCa5.2, TvsCa6.2, TvsCa7.2, TvsCa8.2, TvsCa9.2, TvsCa10.2, TvsCa11.2, TvsCa12.2, TvsCa13.2, TvsCa14.2, TvsCa15.2, TvsCa16.2, TvsCa17.2, TvsCa18.2, TvsCd0.2, TvsCd1.2, TvsCd2.2, TvsCd3.2, TvsCd4.2, TvsCd5.2, TvsCd6.2, TvsCd7.2, TvsD1.2, TvsD2.2, TvsOe.2, TvsScl.2, TvsSda.2, TvsV1.2, TvsV2.2, TvsWe.2, U1.21, U3.14, U5A.10, U5B.10, U5C.10, U5D.10, U5E.10, U5F.10, U5G.10, U5H.10, U5I.10, U6.14, U7A.8, U7B.8, U7C.8, U7C.10, U7C.11, U7D.8, U7E.8, U7F.8, U20A.10, U20B.10, U20C.10, U24.14, U41.14, U328.8, U725.2, U725.13, U1284.11, UPLDA.12, UPLDB.12, UPLDV.12, UPLDX.12, UPLDY.12, Y1.7, Y2.7, Y3.7
I2C_SCL: J36.21, Rcscl.2, TvsScl.1
I2C_SCL_MCU: Rcscl.1, U1284.22
I2C_SDA: J36.3, Rcsda.2, TvsSda.1
I2C_SDA_MCU: Rcsda.1, U1284.23
IRQ_N: U1.4, UPLDY.22
LB_A0: U7D.4, U41.10
LB_A1: U7D.7, U41.9
LB_A2: U7D.9, U41.8
LB_A3: U7D.12, U41.7
LB_A4: U7E.4, U41.6
LB_A5: U7E.7, U41.5
LB_A6: U7E.9, U41.4
LB_A7: U7E.12, U41.3
LB_A8: U7F.4, U41.25
LB_A9: U7F.7, U41.24
LB_A10: U7F.9, U41.21
LB_A11: U7F.12, U41.23
LB_MUX_AB: U7D.1, U7E.1, U7F.1, U1284.17
LB_MUX_G_N: U7D.15, U7E.15, U7F.15
MCU_LB_A0: Rarc2_1.2, U7D.2, U7F.2, U1284.1
MCU_LB_A2: Rarc2_3.2, U7D.11, U7F.11, U1284.3
MCU_LB_A4: Rarc2_5.2, U7E.2, U41.2, U1284.5
MUX_AB: Rphi.2, U1.37, U2.1, U2.2, U7A.1, U7B.1, U7C.1
MUX_G_N: U7A.15, U7B.15, U7C.15
NMI_N: U1.6, UPLDX.14
OE_CART245: U20C.19, UPLDB.19
OE_CPU245: U6.2, U20A.19, UPLDB.15
OE_VID245: U6.1, U20B.19, UPLDB.17
P1_COIN: Rarc1_7.2, U1284.34
P1_COIN_J: J5.7, Rarc1_7.1
P1_DOWN: Rarc1_3.2, U1284.38
P1_DOWN_J: J5.3, Rarc1_3.1
P1_LEFT: Rarc1_2.2, U1284.39
P1_LEFT_J: J5.2, Rarc1_2.1
P1_RIGHT: Rarc1_1.2, U1284.40
P1_RIGHT_J: J5.1, Rarc1_1.1
P1_START: Rarc1_8.2, U1284.33
P1_START_J: J5.8, Rarc1_8.1
P1_UP: Rarc1_4.2, U1284.37
P1_UP_J: J5.4, Rarc1_4.1
P1_X: Rarc1_5.2, U1284.36
P1_X_J: J5.5, Rarc1_5.1
P1_Y: Rarc1_6.2, U1284.35
P1_Y_J: J5.6, Rarc1_6.1
P2_COIN: Rarc2_7.2, U7E.11, U41.1, U1284.7
P2_COIN_J: J6.7, Rarc2_7.1
P2_DOWN_J: J6.3, Rarc2_3.1
P2_LEFT: Rarc2_2.2, U7D.5, U7F.5, U1284.2
P2_LEFT_J: J6.2, Rarc2_2.1
P2_RIGHT_J: J6.1, Rarc2_1.1
P2_START: Rarc2_8.2, U7E.14, U1284.8
P2_START_J: J6.8, Rarc2_8.1
P2_UP: Rarc2_4.2, U7D.14, U7F.14, U1284.4
P2_UP_J: J6.4, Rarc2_4.1
P2_X_J: J6.5, Rarc2_5.1
P2_Y: Rarc2_6.2, U7E.5, U41.26, U1284.6
P2_Y_J: J6.6, Rarc2_6.1
PAD_DATA: Rdata1.1, Rdata2.1, Rpu1.2, U1284.16
PAD_DATA_P1: J3.2, Rdata1.2, TvsD1.1
PAD_DATA_P2: J4.2, Rdata2.2, TvsD2.1
PAD_VCC_P1: Cpad1.1, F2.2, J3.4, TvsV1.1
PAD_VCC_P2: Cpad2.1, F3.2, J4.4, TvsV2.1
PHI2_SRC: Rphi.1, Y1.8
PPU_VA1: U1.32, U3.12, U5A.3, U5B.3, U5C.3, U5D.3, U5E.3, U5F.3, U5G.3, U5H.3, U5I.3, U6.12, U7A.5, U7A.6, U20A.3, U20A.17, U20C.3, U328.3, U1284.25, UPLDB.3
PPU_VA5: U1.28, U3.17, U5A.7, U5B.7, U5C.7, U5D.7, U5E.7, U5F.7, U5G.7, U5H.7, U5I.7, U6.17, U7B.5, U7B.6, U20A.7, U20A.13, U20C.7, U328.11, U1284.29, UPLDB.7
PPU_VA7: U1.26, U3.19, U5A.9, U5B.9, U5C.9, U5D.9, U5E.9, U5F.9, U5G.9, U5H.9, U5I.9, U6.19, U7B.13, U7B.14, U20A.9, U20A.11, U20C.9, U328.13, U1284.21, UPLDB.9
PPU_VA9: U7C.5, U7C.6, UPLDB.11
PROM_A0: U24.10, UPLDV.2
PROM_A1: U24.9, UPLDV.3
PROM_A2: U24.8, UPLDV.4
PROM_A3: U24.7, UPLDV.5
PROM_A4: U24.6, UPLDV.6
PROM_A5: U24.5, UPLDV.7
PROM_D0: RB0.1, U24.11
PROM_D1: RB1.1, U24.12
PROM_D2: RG0.1, U24.13
PROM_D3: RG1.1, U24.15
PROM_D4: RG2.1, U24.16
PROM_D5: RR0.1, U24.17
PROM_D6: RR1.1, U24.18
PROM_D7: RR2.1, U24.19
RASTER_Y0: U5D.19, UPLDY.14
RASTER_Y1: U5D.18, UPLDY.15
RASTER_Y2: U5D.17, UPLDY.16
RASTER_Y3: U5D.16, UPLDY.17
RASTER_Y4: U5D.15, UPLDY.18
RASTER_Y5: U5D.14, UPLDY.19
RASTER_Y6: U5D.13, UPLDY.20
RASTER_Y7: U5D.12, UPLDY.21
RESET_N: J7.3, U1.40, U2.3, UPLDX.13
SCALE_1X: Rscale.1, SW1.1, UPLDV.13
SEL_FE02: U5B.11, U1284.19, UPLDA.15
SEL_FE03: U5C.11, UPLDA.16
SEL_FE04: U5D.11, UPLDA.17
SEL_FE05: U5E.11, UPLDA.18
SEL_FE06: U5A.11, U1284.18, UPLDA.14
SEL_FE08: U5F.11, UPLDA.19
SEL_FE11: UPLDA.23, UPLDB.22, UPLDB.23
SEL_FE90: U5G.11, UPLDA.20
SEL_FE91: U5H.11, UPLDA.21
SEL_FE92: U5I.11, UPLDA.22
VIDEO_B: CinB.1, J2.3, R75B.1, RB0.2, RB1.2
VIDEO_G: CinG.1, J2.2, R75G.1, RG0.2, RG1.2, RG2.2
VIDEO_R: CinR.1, J2.1, R75R.1, RR0.2, RR1.2, RR2.2
VIN_FUSED: F1.2, FB1.1
VIN_PROT: D1.2, F1.1
VIN_RAW: D1.1, J1.1
VRAM_A0: U6.10, U7A.4
VRAM_A1: U6.9, U7A.7
VRAM_A2: U6.8, U7A.9
VRAM_A3: U6.7, U7A.12
VRAM_A4: U6.6, U7B.4
VRAM_A5: U6.5, U7B.7
VRAM_A6: U6.4, U7B.9
VRAM_A7: U6.3, U7B.12
VRAM_A8: U6.25, U7C.4
VRAM_A9: U6.24, U7C.7
VRAM_A10: U6.21, U7C.9
VRAM_A11: U6.23, U7C.12
XTAL328: Cxtal5a.1, U328.9, Y5.1
XTAL328b: Cxtal5b.1, U328.10, Y5.2
XTAL1284: Cxtal4a.1, U1284.13, Y4.1
XTAL1284b: Cxtal4b.1, U1284.12, Y4.2
YTRAP: Lytrap.1, U725.12
YTRAP_MID: Cytrap.1, Lytrap.2

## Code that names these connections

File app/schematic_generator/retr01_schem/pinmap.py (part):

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UPLDY_LE_FE04 = "23"  # raster Y load enable
UPLDY_EQ = "22"

# UPLDV compositor + CART_A14-A18 MAP high export (1284 GPIO budget exhausted).
UPLDV_IDX = {i: str(2 + i) for i in range(6)}
UPLDV_SCALE, UPLDV_EQ = "13", "14"
UPLDV_CART_A = {14 + i: str(15 + i) for i in range(5)}  # A14..A18 -> pins 15..19
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M1284_HBLANK = "17"  # PD3
M1284_FE06, M1284_FE07 = "18", "19"  # PD4/PD5 (BG0 scroll). SEL_FE00 shares UPLDA pin with FE06.
# Soft $FExx: palette + MAP seek strobes. Only PD0/PD1 free after DQ remap.
M1284_FE08 = "14"  # PD0 SEL_FE08 palette addr
M1284_FE90 = "15"  # PD1 SEL_FE90 MAP lo (FE91/FE92 also strobe via UPLDV_LE_MAP path)
M1284_XTAL2, M1284_XTAL1 = "12", "13"
# Prefer PC2-PC7 + PD6-PD7 for DQ to free PD2-5:
M1284_DQ = ("24", "25", "26", "27", "28", "29", "20", "21")  # PC2-7, PD6-7
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M328_RESET, M328_VCC, M328_GND = "1", "7", "8"
M328_XTAL1, M328_XTAL2 = "9", "10"
M328_DQ = ("2", "3", "4", "5", "6", "11", "12", "13")  # PD0-4, PD5-7
M328_AUD = ("14", "15", "16", "17", "18", "19", "23", "24")  # PB0-5, PC0-1 = AUD0(LSB)..AUD7(MSB)

# AD725 RGB->NTSC/PAL encoder (wide SOIC-16 on DIP-16 via Proto Advantage PA0006).
AD725_STND, AD725_AGND, AD725_4FSC, AD725_APOS = "1", "2", "3", "4"
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
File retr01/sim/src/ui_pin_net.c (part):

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                              "SEL_FE02");
    pin_net_link_latch_le_pld(g, pld, r01s_sn74hc573_entity(board->io_latch_impl.latch573[R01S_LATCH_FE03]),
                              "SEL_FE03");
    pin_net_link_latch_le_pld(g, pld, raster, "SEL_FE04");
    pin_net_link_latch_le_pld(g, pld, fe10, "SEL_FE10");
    pin_net_link_latch_le_pld(g, pld, fe11, "SEL_FE11");
    pin_net_link_latch_le_pld(g, pld, r01s_sn74hc573_entity(board->io_latch_impl.latch573[R01S_LATCH_FE08]),
                              "SEL_FE08");
    pin_net_link_latch_le_pld(g, pld, r01s_sn74hc573_entity(board->io_latch_impl.latch573[R01S_LATCH_FE90]),
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        pin_net_link(g, flash, dq, buf_cart, an);
    }

    pin_net_link(g, beam, "DOT", dot_osc, "DOT");
    pin_net_link_beam_y_beam(g, beam_y, beam);
    pin_net_link_beam_y_raster(g, beam_y, raster);
    pin_net_link(g, cpu, "IRQB", beam_y, "EQ#");
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    pin_net_link(g, sram_lb, "A2", mux_lb, "3Y");
    pin_net_link(g, sram_lb, "A3", mux_lb, "4Y");

    pin_net_link(g, cpu, "PHI2", osc, "PHI2");
    pin_net_link(g, hc, "1A", osc, "PHI2");
    pin_net_link(g, cpu, "PHI2", hc, "1Y");
    pin_net_link(g, hc, "2A", cpu, "RESB");
}

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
